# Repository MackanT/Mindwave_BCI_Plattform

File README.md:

# mindwave_car_controller
C Code to control robotic car through mindwave mobile 2

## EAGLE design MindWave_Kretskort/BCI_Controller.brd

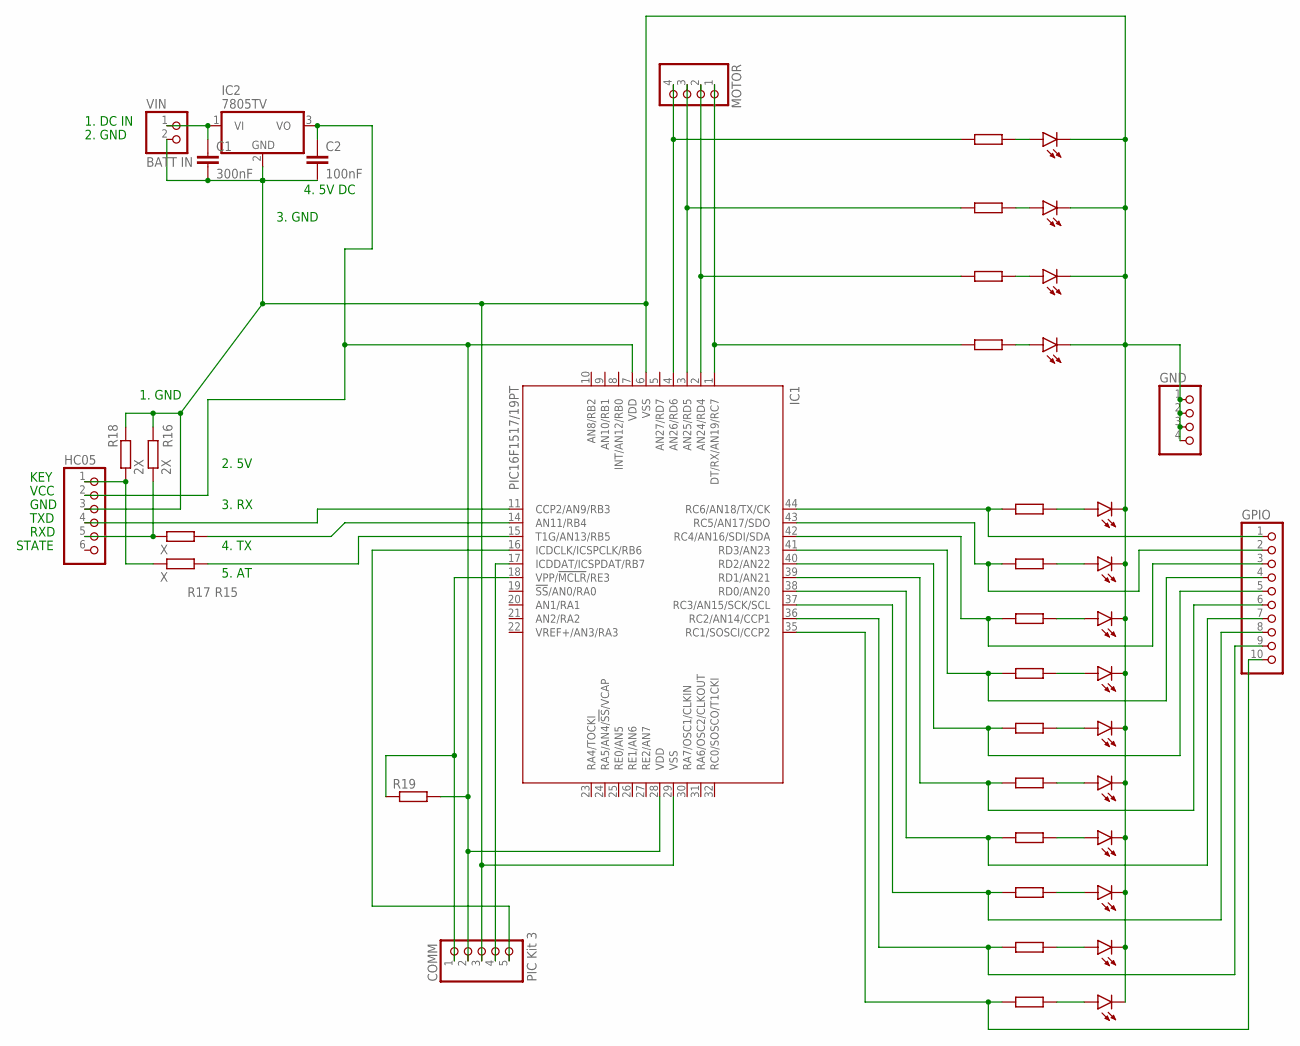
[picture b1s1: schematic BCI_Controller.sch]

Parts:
C1: 300nF; C1206
C2: 100nF; C1206
COMM: PIC Kit 3; 1X05
GND: PINHD-1X4; 1X04
GPIO: PINHD-1X10; 1X10
HC05: PINHD-1X6; 1X06
IC1: PIC16F1517/19PT; TQFP44
IC2: 7805TV; TO220V
LED1, LED2, LED3, LED4, LED5, LED6, LED7, LED8, LED9, LED10, LED11, LED12, LED13, LED14: LEDSMT1206; 1206
MOTOR: PINHD-1X4; 1X04
R1, R2, R3, R4, R5, R6, R7, R8, R9, R10, R11, R12, R13, R14: R-EU_R1206; R1206
R15, R17: X; M1206
R16, R18: 2X; M1206
R19: R-EU_M1206; M1206
VIN: BATT IN; 1X02

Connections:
unnamed: C1.1, IC2.1 (VI), VIN.1
unnamed: COMM.4, IC1.17 (ICDDAT/ICSPDAT/RB7)
unnamed: LED1.A, R1.2
unnamed: LED2.A, R2.2
unnamed: COMM.5, IC1.16 (ICDCLK/ICSPCLK/RB6)
unnamed: GPIO.1, IC1.44 (RC6/AN18/TX/CK), R1.1
unnamed: GPIO.2, IC1.43 (RC5/AN17/SDO), R2.1
unnamed: GPIO.3, IC1.42 (RC4/AN16/SDI/SDA), R3.1
unnamed: GPIO.4, IC1.41 (RD3/AN23), R4.1
unnamed: GPIO.5, IC1.40 (RD2/AN22), R5.1
unnamed: GPIO.6, IC1.39 (RD1/AN21), R6.1
unnamed: GPIO.7, IC1.38 (RD0/AN20), R7.1
unnamed: GPIO.8, IC1.37 (RC3/AN15/SCK/SCL), R8.1
unnamed: GPIO.9, IC1.36 (RC2/AN14/CCP1), R9.1
unnamed: GPIO.10, IC1.35 (RC1/SOSCI/CCP2), R10.1
unnamed: LED3.A, R3.2
unnamed: LED4.A, R4.2
unnamed: LED5.A, R5.2
unnamed: LED6.A, R6.2
unnamed: LED7.A, R7.2
unnamed: LED8.A, R8.2
unnamed: LED9.A, R9.2
unnamed: LED10.A, R10.2
unnamed: HC05.5, R15.1, R16.1
unnamed: IC1.14 (AN11/RB4), R15.2
unnamed: IC1.3 (AN25/RD5), MOTOR.3, R12.1
unnamed: IC1.4 (AN26/RD6), MOTOR.4, R11.1
unnamed: LED14.A, R11.2
unnamed: LED13.A, R12.2
unnamed: LED12.A, R13.2
unnamed: LED11.A, R14.2
unnamed: IC1.2 (AN24/RD4), MOTOR.2, R13.1
unnamed: IC1.1 (DT/RX/AN19/RC7), MOTOR.1, R14.1
unnamed: HC05.1, R17.1, R18.1
unnamed: C2.1, COMM.2, HC05.2, IC1.7 (VDD), IC1.28 (VDD), IC2.3 (VO), R19.2
unnamed: IC1.15 (T1G/AN13/RB5), R17.2
unnamed: COMM.1, IC1.18 (VPP/!MCLR!/RE3), R19.1
unnamed: HC05.4, IC1.11 (CCP2/AN9/RB3)
unnamed: C1.2, C2.2, COMM.3, GND.1, GND.2, GND.3, GND.4, HC05.3, IC1.6 (VSS), IC1.29 (VSS), IC2.2 (GND), LED1.C, LED2.C, LED3.C, LED4.C, LED5.C, LED6.C, LED7.C, LED8.C, LED9.C, LED10.C, LED11.C, LED12.C, LED13.C, LED14.C, R16.2, R18.2, VIN.2

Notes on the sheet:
KEY
VCC
GND
TXD
RXD
STATE
1. GND
2. 5V
3. RX
4. TX
5. AT
1. DC IN
2. GND
3. GND
4. 5V DC

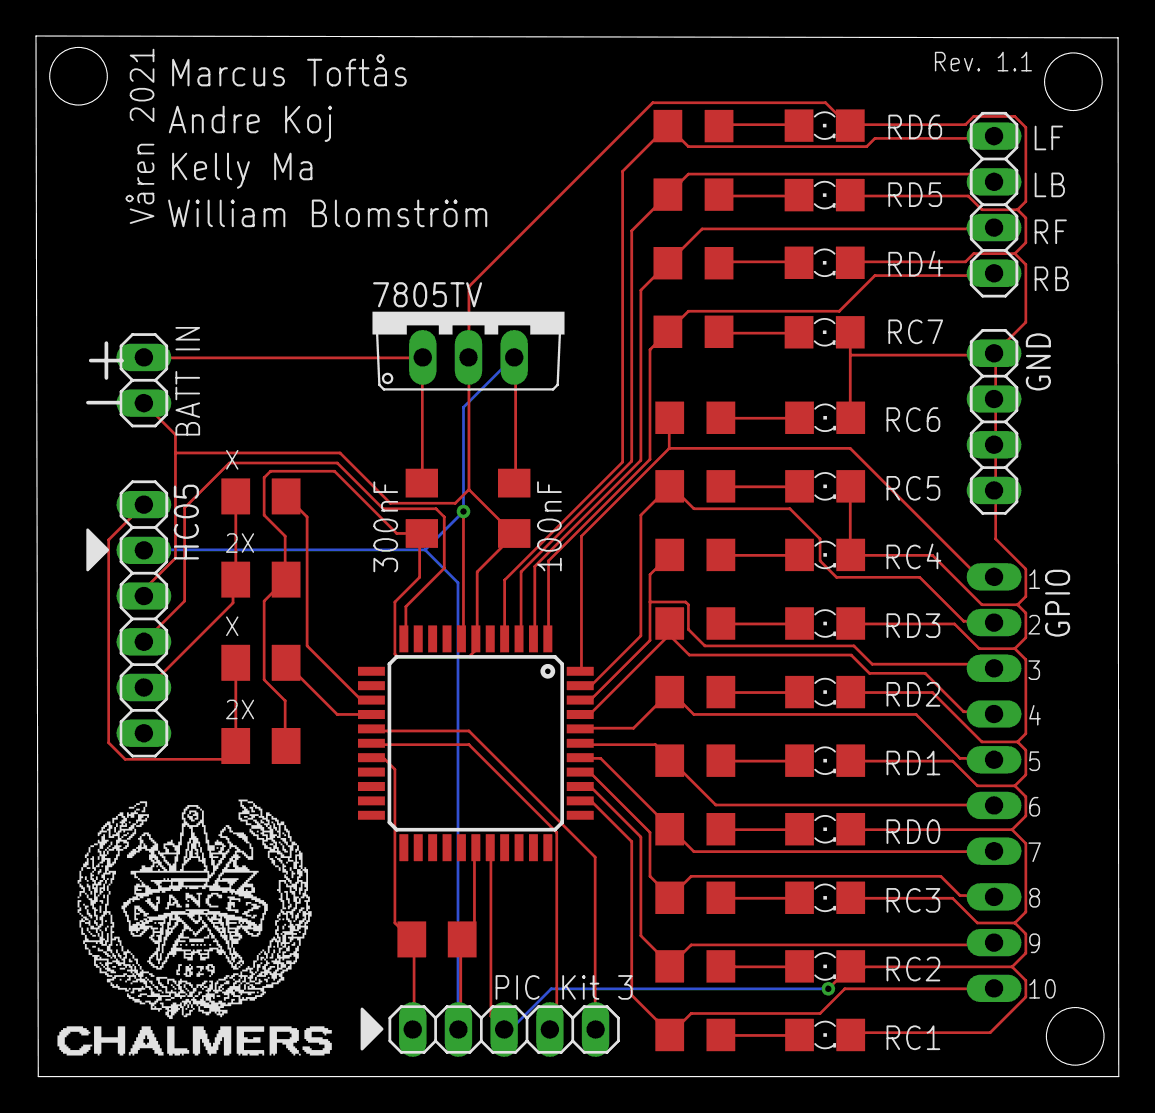
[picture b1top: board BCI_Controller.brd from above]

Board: 2 copper layers, 60.2 x 57.8 mm, 43 parts (1 on the bottom side), 39 nets.

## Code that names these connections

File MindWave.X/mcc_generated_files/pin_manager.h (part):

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#define RB3_SetHigh()            do { LATBbits.LATB3 = 1; } while(0)
#define RB3_SetLow()             do { LATBbits.LATB3 = 0; } while(0)
#define RB3_Toggle()             do { LATBbits.LATB3 = ~LATBbits.LATB3; } while(0)
#define RB3_GetValue()              PORTBbits.RB3
#define RB3_SetDigitalInput()    do { TRISBbits.TRISB3 = 1; } while(0)
#define RB3_SetDigitalOutput()   do { TRISBbits.TRISB3 = 0; } while(0)
#define RB3_SetPullup()             do { WPUBbits.WPUB3 = 1; } while(0)
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// get/set KEY_AT aliases
#define KEY_AT_TRIS                 TRISBbits.TRISB5
#define KEY_AT_LAT                  LATBbits.LATB5
#define KEY_AT_PORT                 PORTBbits.RB5
#define KEY_AT_WPU                  WPUBbits.WPUB5
#define KEY_AT_OD                   ODCONBbits.ODB5
#define KEY_AT_ANS                  ANSELBbits.ANSB5
#define KEY_AT_SetHigh()            do { LATBbits.LATB5 = 1; } while(0)
#define KEY_AT_SetLow()             do { LATBbits.LATB5 = 0; } while(0)
#define KEY_AT_Toggle()             do { LATBbits.LATB5 = ~LATBbits.LATB5; } while(0)
#define KEY_AT_GetValue()           PORTBbits.RB5
#define KEY_AT_SetDigitalInput()    do { TRISBbits.TRISB5 = 1; } while(0)
#define KEY_AT_SetDigitalOutput()   do { TRISBbits.TRISB5 = 0; } while(0)
#define KEY_AT_SetPullup()          do { WPUBbits.WPUB5 = 1; } while(0)
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#define RC1_SetHigh()            do { LATCbits.LATC1 = 1; } while(0)
#define RC1_SetLow()             do { LATCbits.LATC1 = 0; } while(0)
#define RC1_Toggle()             do { LATCbits.LATC1 = ~LATCbits.LATC1; } while(0)
#define RC1_GetValue()              PORTCbits.RC1
#define RC1_SetDigitalInput()    do { TRISCbits.TRISC1 = 1; } while(0)
#define RC1_SetDigitalOutput()   do { TRISCbits.TRISC1 = 0; } while(0)
#define RC1_SetPullup()             do { WPUCbits.WPUC1 = 1; } while(0)
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// get/set G9 aliases
#define G9_TRIS                 TRISCbits.TRISC2
#define G9_LAT                  LATCbits.LATC2
#define G9_PORT                 PORTCbits.RC2
#define G9_WPU                  WPUCbits.WPUC2
#define G9_OD                   ODCONCbits.ODC2
#define G9_ANS                  ANSELCbits.ANSC2
#define G9_SetHigh()            do { LATCbits.LATC2 = 1; } while(0)
#define G9_SetLow()             do { LATCbits.LATC2 = 0; } while(0)
#define G9_Toggle()             do { LATCbits.LATC2 = ~LATCbits.LATC2; } while(0)
#define G9_GetValue()           PORTCbits.RC2
#define G9_SetDigitalInput()    do { TRISCbits.TRISC2 = 1; } while(0)
#define G9_SetDigitalOutput()   do { TRISCbits.TRISC2 = 0; } while(0)
#define G9_SetPullup()          do { WPUCbits.WPUC2 = 1; } while(0)
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// get/set G8 aliases
#define G8_TRIS                 TRISCbits.TRISC3
#define G8_LAT                  LATCbits.LATC3
#define G8_PORT                 PORTCbits.RC3
#define G8_WPU                  WPUCbits.WPUC3
#define G8_OD                   ODCONCbits.ODC3
#define G8_ANS                  ANSELCbits.ANSC3
#define G8_SetHigh()            do { LATCbits.LATC3 = 1; } while(0)
#define G8_SetLow()             do { LATCbits.LATC3 = 0; } while(0)
#define G8_Toggle()             do { LATCbits.LATC3 = ~LATCbits.LATC3; } while(0)
#define G8_GetValue()           PORTCbits.RC3
#define G8_SetDigitalInput()    do { TRISCbits.TRISC3 = 1; } while(0)
#define G8_SetDigitalOutput()   do { TRISCbits.TRISC3 = 0; } while(0)
#define G8_SetPullup()          do { WPUCbits.WPUC3 = 1; } while(0)
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// get/set G3 aliases
#define G3_TRIS                 TRISCbits.TRISC4
#define G3_LAT                  LATCbits.LATC4
#define G3_PORT                 PORTCbits.RC4
#define G3_WPU                  WPUCbits.WPUC4
#define G3_OD                   ODCONCbits.ODC4
#define G3_ANS                  ANSELCbits.ANSC4
#define G3_SetHigh()            do { LATCbits.LATC4 = 1; } while(0)
#define G3_SetLow()             do { LATCbits.LATC4 = 0; } while(0)
#define G3_Toggle()             do { LATCbits.LATC4 = ~LATCbits.LATC4; } while(0)
#define G3_GetValue()           PORTCbits.RC4
#define G3_SetDigitalInput()    do { TRISCbits.TRISC4 = 1; } while(0)
#define G3_SetDigitalOutput()   do { TRISCbits.TRISC4 = 0; } while(0)
#define G3_SetPullup()          do { WPUCbits.WPUC4 = 1; } while(0)
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// get/set G2 aliases
#define G2_TRIS                 TRISCbits.TRISC5
#define G2_LAT                  LATCbits.LATC5
#define G2_PORT                 PORTCbits.RC5
#define G2_WPU                  WPUCbits.WPUC5
#define G2_OD                   ODCONCbits.ODC5
#define G2_ANS                  ANSELCbits.ANSC5
#define G2_SetHigh()            do { LATCbits.LATC5 = 1; } while(0)
#define G2_SetLow()             do { LATCbits.LATC5 = 0; } while(0)
#define G2_Toggle()             do { LATCbits.LATC5 = ~LATCbits.LATC5; } while(0)
#define G2_GetValue()           PORTCbits.RC5
#define G2_SetDigitalInput()    do { TRISCbits.TRISC5 = 1; } while(0)
#define G2_SetDigitalOutput()   do { TRISCbits.TRISC5 = 0; } while(0)
#define G2_SetPullup()          do { WPUCbits.WPUC5 = 1; } while(0)
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// get/set G1 aliases
#define G1_TRIS                 TRISCbits.TRISC6
#define G1_LAT                  LATCbits.LATC6
#define G1_PORT                 PORTCbits.RC6
#define G1_WPU                  WPUCbits.WPUC6
#define G1_OD                   ODCONCbits.ODC6
#define G1_ANS                  ANSELCbits.ANSC6
#define G1_SetHigh()            do { LATCbits.LATC6 = 1; } while(0)
#define G1_SetLow()             do { LATCbits.LATC6 = 0; } while(0)
#define G1_Toggle()             do { LATCbits.LATC6 = ~LATCbits.LATC6; } while(0)
#define G1_GetValue()           PORTCbits.RC6
#define G1_SetDigitalInput()    do { TRISCbits.TRISC6 = 1; } while(0)
#define G1_SetDigitalOutput()   do { TRISCbits.TRISC6 = 0; } while(0)
#define G1_SetPullup()          do { WPUCbits.WPUC6 = 1; } while(0)
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// get/set M_RB aliases
#define M_RB_TRIS                 TRISCbits.TRISC7
#define M_RB_LAT                  LATCbits.LATC7
#define M_RB_PORT                 PORTCbits.RC7
#define M_RB_WPU                  WPUCbits.WPUC7
#define M_RB_OD                   ODCONCbits.ODC7
#define M_RB_ANS                  ANSELCbits.ANSC7
#define M_RB_SetHigh()            do { LATCbits.LATC7 = 1; } while(0)
#define M_RB_SetLow()             do { LATCbits.LATC7 = 0; } while(0)
#define M_RB_Toggle()             do { LATCbits.LATC7 = ~LATCbits.LATC7; } while(0)
#define M_RB_GetValue()           PORTCbits.RC7
#define M_RB_SetDigitalInput()    do { TRISCbits.TRISC7 = 1; } while(0)
#define M_RB_SetDigitalOutput()   do { TRISCbits.TRISC7 = 0; } while(0)
#define M_RB_SetPullup()          do { WPUCbits.WPUC7 = 1; } while(0)
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// get/set G7 aliases
#define G7_TRIS                 TRISDbits.TRISD0
#define G7_LAT                  LATDbits.LATD0
#define G7_PORT                 PORTDbits.RD0
#define G7_WPU                  WPUDbits.WPUD0
#define G7_OD                   ODCONDbits.ODD0
#define G7_ANS                  ANSELDbits.ANSD0
#define G7_SetHigh()            do { LATDbits.LATD0 = 1; } while(0)
#define G7_SetLow()             do { LATDbits.LATD0 = 0; } while(0)
#define G7_Toggle()             do { LATDbits.LATD0 = ~LATDbits.LATD0; } while(0)
#define G7_GetValue()           PORTDbits.RD0
#define G7_SetDigitalInput()    do { TRISDbits.TRISD0 = 1; } while(0)
#define G7_SetDigitalOutput()   do { TRISDbits.TRISD0 = 0; } while(0)
#define G7_SetPullup()          do { WPUDbits.WPUD0 = 1; } while(0)
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// get/set G6 aliases
#define G6_TRIS                 TRISDbits.TRISD1
#define G6_LAT                  LATDbits.LATD1
#define G6_PORT                 PORTDbits.RD1
#define G6_WPU                  WPUDbits.WPUD1
#define G6_OD                   ODCONDbits.ODD1
#define G6_ANS                  ANSELDbits.ANSD1
#define G6_SetHigh()            do { LATDbits.LATD1 = 1; } while(0)
#define G6_SetLow()             do { LATDbits.LATD1 = 0; } while(0)
#define G6_Toggle()             do { LATDbits.LATD1 = ~LATDbits.LATD1; } while(0)
#define G6_GetValue()           PORTDbits.RD1
#define G6_SetDigitalInput()    do { TRISDbits.TRISD1 = 1; } while(0)
#define G6_SetDigitalOutput()   do { TRISDbits.TRISD1 = 0; } while(0)
#define G6_SetPullup()          do { WPUDbits.WPUD1 = 1; } while(0)
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// get/set G5 aliases
#define G5_TRIS                 TRISDbits.TRISD2
#define G5_LAT                  LATDbits.LATD2
#define G5_PORT                 PORTDbits.RD2
#define G5_WPU                  WPUDbits.WPUD2
#define G5_OD                   ODCONDbits.ODD2
#define G5_ANS                  ANSELDbits.ANSD2
#define G5_SetHigh()            do { LATDbits.LATD2 = 1; } while(0)
#define G5_SetLow()             do { LATDbits.LATD2 = 0; } while(0)
#define G5_Toggle()             do { LATDbits.LATD2 = ~LATDbits.LATD2; } while(0)
#define G5_GetValue()           PORTDbits.RD2
#define G5_SetDigitalInput()    do { TRISDbits.TRISD2 = 1; } while(0)
#define G5_SetDigitalOutput()   do { TRISDbits.TRISD2 = 0; } while(0)
#define G5_SetPullup()          do { WPUDbits.WPUD2 = 1; } while(0)
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// get/set G4 aliases
#define G4_TRIS                 TRISDbits.TRISD3
#define G4_LAT                  LATDbits.LATD3
#define G4_PORT                 PORTDbits.RD3
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
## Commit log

2021-02-22 PIC-C Version
2021-05-11 Files for the utilized motherboard

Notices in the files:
MindWave.X/mcc_generated_files/pin_manager.h:
(c) 2018 Microchip Technology Inc. and its subsidiaries.
